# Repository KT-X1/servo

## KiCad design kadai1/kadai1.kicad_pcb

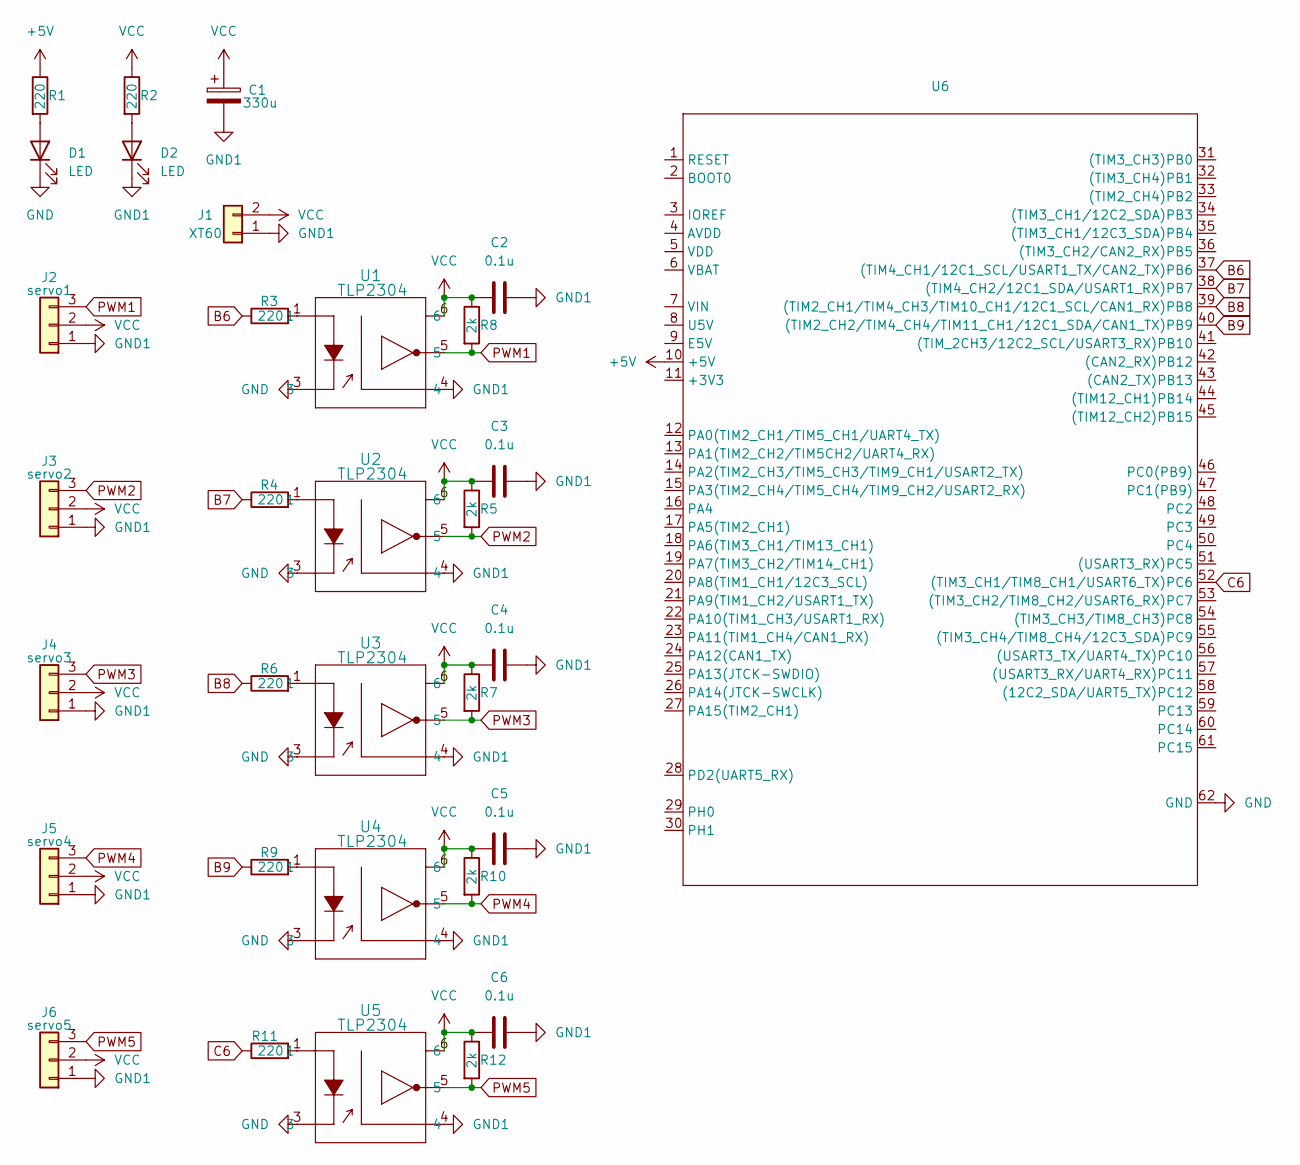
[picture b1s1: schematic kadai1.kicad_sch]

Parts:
C1: 330u; CP_Radial_D5.0mm_P2.00mm
C2, C3, C4, C5, C6: 0.1u; C_Disc_D3.0mm_W1.6mm_P2.50mm
D1, D2: LED; LED_D3.0mm
J1: XT60; AMASS_XT60PW-M_1x02_P7.20mm_Horizontal
J2: servo1; PinHeader_1x03_P2.54mm_Vertical
J3: servo2; PinHeader_1x03_P2.54mm_Vertical
J4: servo3; PinHeader_1x03_P2.54mm_Vertical
J5: servo4; PinHeader_1x03_P2.54mm_Vertical
J6: servo5; PinHeader_1x03_P2.54mm_Vertical
R1, R2, R3, R4, R6, R9, R11: 220; R_Axial_DIN0207_L6.3mm_D2.5mm_P10.16mm_Horizontal
R5, R7, R8, R10, R12: 2k; R_Axial_DIN0207_L6.3mm_D2.5mm_P10.16mm_Horizontal
U1, U2, U3, U4, U5: TLP2304; 5pin SO6_TOS
U6: STM32F446RE_Nucleo

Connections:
+5V: R1.1, U6.10 (+5V)
B6: R3.1, U6.37 ((TIM4_CH1/12C1_SCL/USART1_TX/CAN2_TX)PB6)
B7: R4.1, U6.38 ((TIM4_CH2/12C1_SDA/USART1_RX)PB7)
B8: R6.1, U6.39 ((TIM2_CH1/TIM4_CH3/TIM10_CH1/12C1_SCL/C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)
B9: R9.1, U6.40 ((TIM2_CH2/TIM4_CH4/TIM11_CH1/12C1_SDA/C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)
C6: R11.1, U6.52 ((TIM3_CH1/TIM8_CH1/USART6_TX)PC6)
GND: D1.1 (K), U1.3, U2.3, U3.3, U4.3, U5.3, U6.62 (GND)
GND1: C1.2, C2.2, C3.2, C4.2, C5.2, C6.2, D2.1 (K), J1.1, J2.1, J3.1, J4.1, J5.1, J6.1, U1.4, U2.4, U3.4, U4.4, U5.4
unnamed: D1.2 (A), R1.2
unnamed: D2.2 (A), R2.2
unnamed: R3.2, U1.1
unnamed: R4.2, U2.1
unnamed: R6.2, U3.1
unnamed: R9.2, U4.1
unnamed: R11.2, U5.1
PWM1: J2.3, R8.2, U1.5
PWM2: J3.3, R5.2, U2.5
PWM3: J4.3, R7.2, U3.5
PWM4: J5.3, R10.2, U4.5
PWM5: J6.3, R12.2, U5.5
VCC: C1.1, C2.1, C3.1, C4.1, C5.1, C6.1, J1.2, J2.2, J3.2, J4.2, J5.2, J6.2, R2.1, R5.1, R7.1, R8.1, R10.1, R12.1, U1.6, U2.6, U3.6, U4.6, U5.6

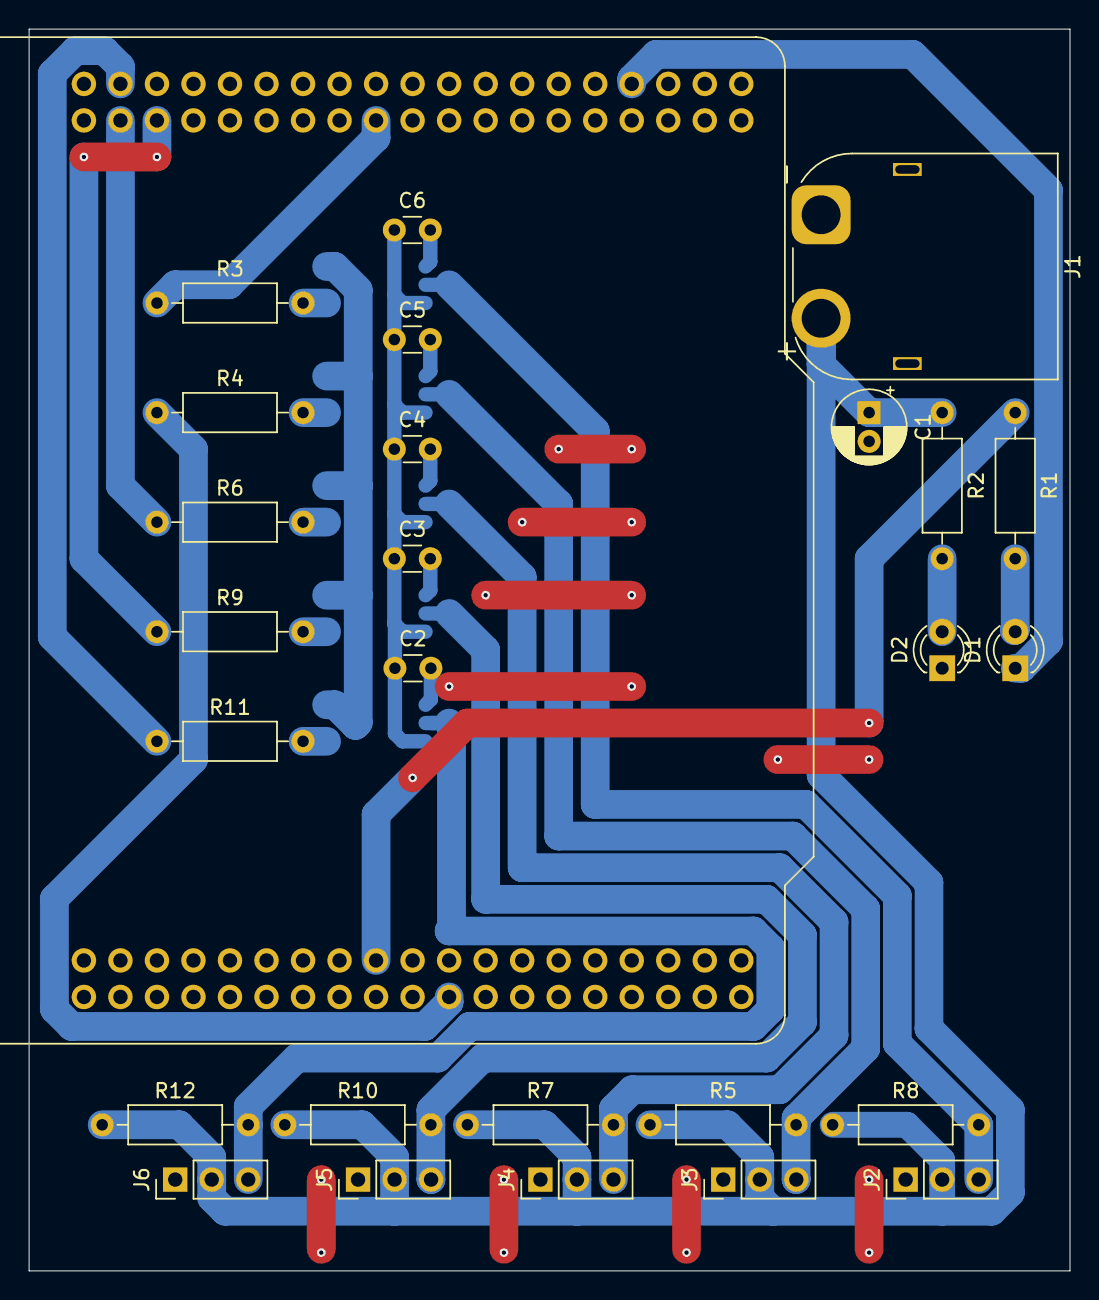
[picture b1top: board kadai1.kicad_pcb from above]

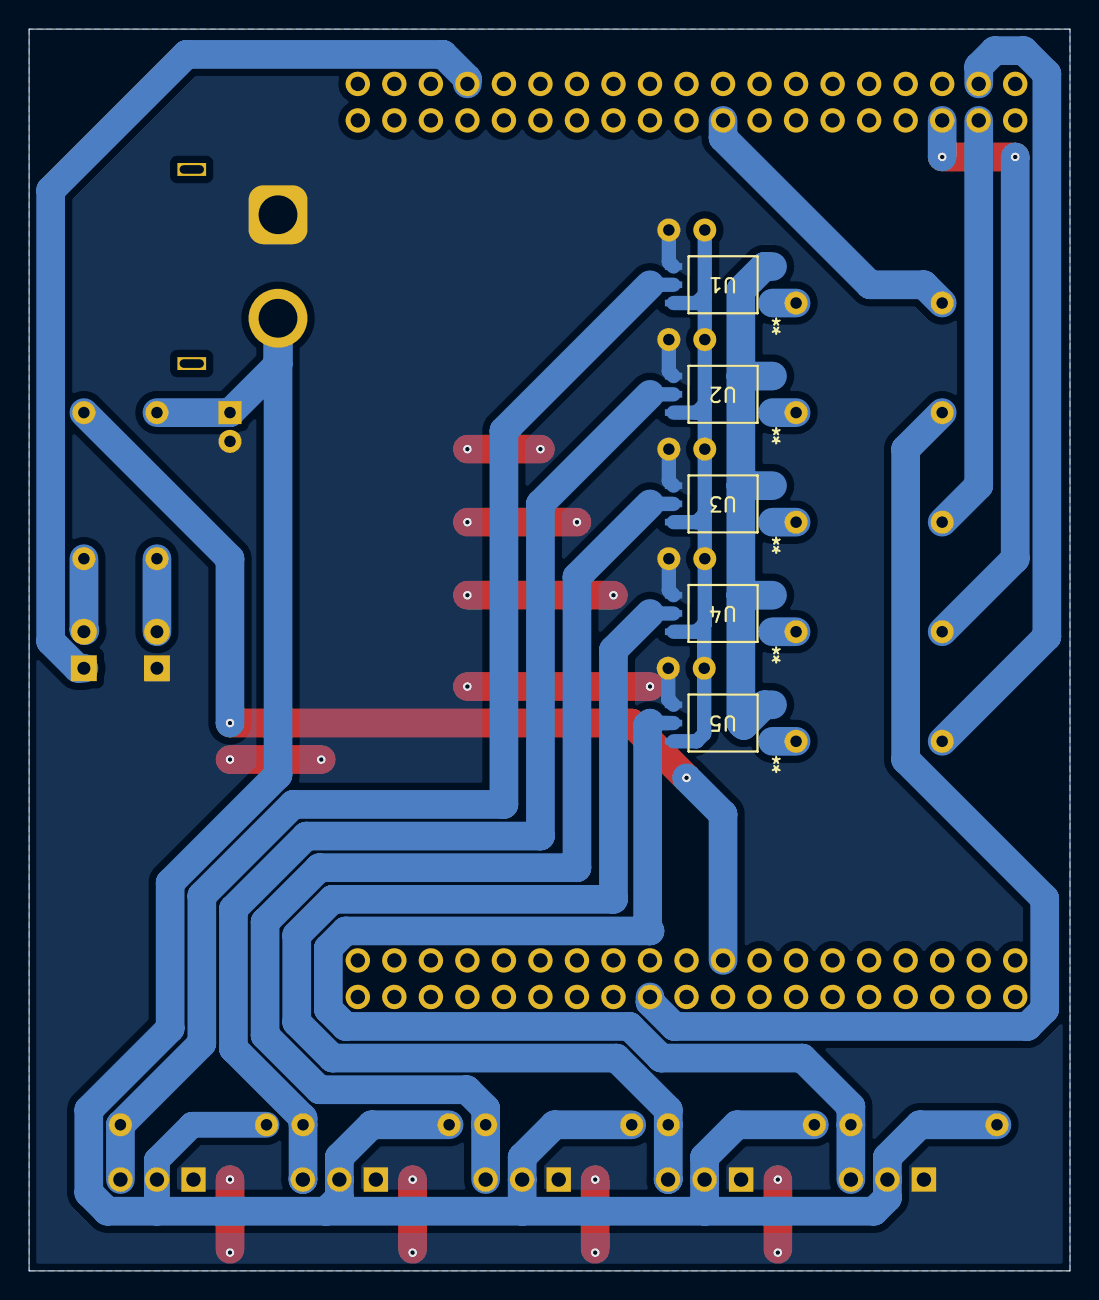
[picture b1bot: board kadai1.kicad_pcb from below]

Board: 2 copper layers, 72.4 x 86.4 mm, 32 parts (5 on the bottom side), 21 nets.
